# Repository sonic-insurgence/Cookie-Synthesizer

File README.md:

# Cookie Synthesizer

The Cookie is a small but powerful DIY synthesizer project.
It is derived from the Shruthi-1 DIY hybrid synthesizer by Émilie Gillet 
from Mutable Instruments. 
Slight modifications have been carried out concerning the PCB form factor, the track layout 
and the arrangement of components. 
The circuit is basically the same as the "Shruthi-Digital-v08" with a "Shruthi-Analog-SMR4-mkII-v02" 
filter board.

### User Manual
Learn how to operate your Cookie Synth by having a look at the 
[user manual of the original Shruthi-1](https://mutable-instruments.net/archive/shruthi/manual/).

### Patch Editor
There are several editors out there that can be used to tweak the sounds on your Cookie Synth. 
E. g. check out the one from 
[Ixox (Win / OS X)](https://github.com/Ixox/Shruthi-And-Ambika-Editors/releases).
You may also find a patch manager software useful to organize your many sounds. 
If you are on Windows you might give  
[ShruthiFi1_0 (Win)](https://sites.google.com/site/thesonicfunk/programs) a try, although 
I had some issues with it.

### Firmware
The Cookie provides full software compatibility with Shruthi-1. You can flash the 
microcontroller with the original firmware from MI or with an alternative firmware like 
YAM by bjoeri. The software provided in this repository is a slight modification of the latter.
* https://github.com/pichenettes/shruthi-1
* https://github.com/bjoeri/shruthi-1

### Authors
* Author of the derived work, i. e. the Cookie synthesizer, is Sonic Insurgence.
* Author of the original work, i. e. the Shruthi-1 synthesizer, is Émilie Gillet.
* Author of the alternative firmware YAM is bjoeri.

### License
The Cookie schematics and PCB design files are licensed under a CreativeCommons CC-BY-SA license.
See: http://creativecommons.org/licenses/by-sa/3.0/

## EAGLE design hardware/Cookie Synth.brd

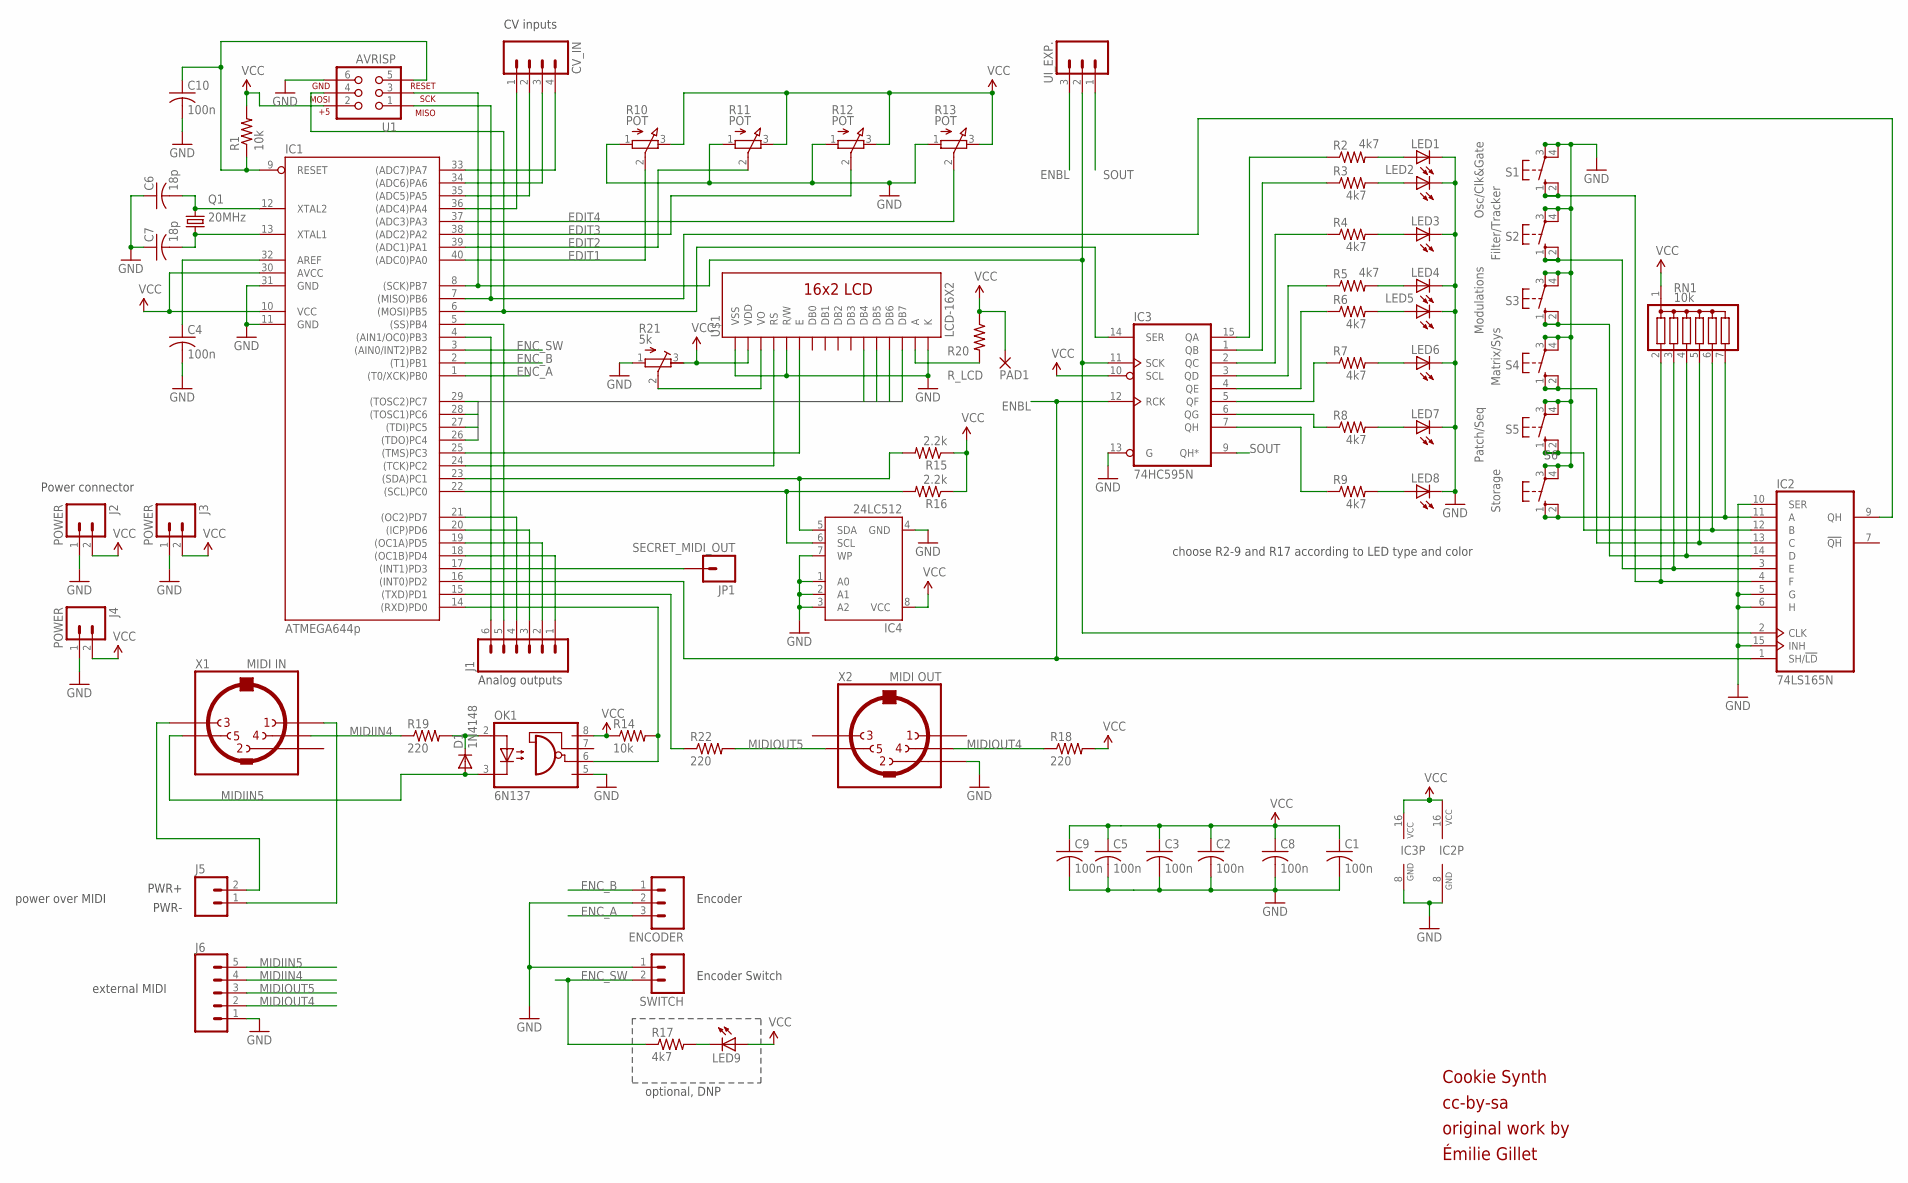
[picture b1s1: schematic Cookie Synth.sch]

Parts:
C1, C2, C3, C4, C5, C8, C9, C10: 100n; C025-024X044
C6, C7: 18p; C025-024X044
CV_IN: M04PTH; 1X04
D1: 1N4148; D-5
ENCODER: M03PTH; 1X03
IC1: ATMEGA644p; DIL40
IC2: 74LS165N; DIL16
IC3: 74HC595N; DIL16
IC4: 24LC512; DIL08
J1: M06SIP; 1X06
J2, J3, J4: POWER; 1X02
J5: M02PTH; 1X02
J6: CONN_05; 1X05
JP1: SECRET_MIDI_OUT; 1X01
LED1, LED2, LED3, LED4, LED5, LED6, LED7, LED8, LED9: LED3MM
OK1: 6N137; DIL08
PAD1: 1,6/0,8
Q1: 20MHz; HC49U-V
R1, R14: 10k; 0204/7
R2, R3, R4, R5, R6, R7, R8, R9, R17: 4k7; 0204/7
R10, R11, R12, R13: POT; POTI_ALPS_RK09
R15, R16: 2.2k; 0204/7
R18, R19, R22: 220; 0204/7
R20: R_LCD; 0204/7
R21: 5k; RTRIM3296X
RN1: 10k; SIL7
S1: Osc/Clk&Gate; B3F-40XX
S2: Filter/Tracker; B3F-40XX
S3: Modulations; B3F-40XX
S4: Matrix/Sys; B3F-40XX
S5: Patch/Seq; B3F-40XX
S6: Storage; B3F-40XX
SWITCH: M02PTH; 1X02
U1: AVRISP; 2X3
U$1: LCD-16X2
UI_EXP.: M03PTH; 1X03
X1: MIDI IN; MAB5SH
X2: MIDI OUT; MAB5SH

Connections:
EDIT1: IC1.40 ((ADC0)PA0), R10.2 (S)
EDIT2: IC1.39 ((ADC1)PA1), R11.2 (S)
EDIT3: IC1.38 ((ADC2)PA2), R12.2 (S)
EDIT4: IC1.37 ((ADC3)PA3), R13.2 (S)
ENBL: IC1.16 ((INT0)PD2), IC2.1 (SH/!LD), IC3.12 (RCK), UI_EXP..3
ENC_A: ENCODER.3, IC1.1 ((T0/XCK)PB0)
ENC_B: ENCODER.1, IC1.2 ((T1)PB1)
ENC_SW: IC1.3 ((AIN0/INT2)PB2), R17.1, SWITCH.2
GND: C1.2, C2.2, C3.2, C4.2, C5.2, C6.1, C7.1, C8.2, C9.2, C10.2, ENCODER.2, IC1.11 (GND), IC1.31 (GND), IC2.5 (G), IC2.6 (H), IC2.8 (GND), IC2.10 (SER), IC2.15 (INH), IC3.8 (GND), IC3.13 (G), IC4.1 (A0), IC4.2 (A1), IC4.3 (A2), IC4.4 (GND), IC4.7 (WP), J2.1, J3.1, J4.1, J6.1, LED1.K (C), LED2.K (C), LED3.K (C), LED4.K (C), LED5.K (C), LED6.K (C), LED7.K (C), LED8.K (C), OK1.5 (GND), R10.1 (A), R11.1 (A), R12.1 (A), R13.1 (A), R21.1 (E), S1.3, S1.4 (P1), S2.3, S2.4 (P1), S3.3, S3.4 (P1), S4.3, S4.4 (P1), S5.3, S5.4 (P1), S6.3, S6.4 (P1), SWITCH.1, U1.6, U$1.1 (VSS), U$1.5 (R/W), U$1.16 (K), X2.2
LCD_DATA1: IC1.26 ((TDO)PC4), U$1.11 (DB4)
LCD_DATA2: IC1.27 ((TDI)PC5), U$1.12 (DB5)
LCD_DATA3: IC1.28 ((TOSC1)PC6), U$1.13 (DB6)
LCD_DATA4: IC1.29 ((TOSC2)PC7), U$1.14 (DB7)
MIDIIN4: J6.4, R19.1, X1.4
MIDIIN5: D1.A, J6.5, OK1.3 (C), X1.5
MIDIOUT4: J6.2, R18.1, X2.4
MIDIOUT5: J6.3, R22.2, X2.5
unnamed: IC3.2 (QC), R4.1
unnamed: IC1.24 ((TCK)PC2), U$1.4 (RS)
unnamed: IC2.11 (A), RN1.7, S6.1 (S), S6.2 (S1)
unnamed: LED9.K (C), R17.2
unnamed: IC2.3 (E), RN1.3, S2.1 (S), S2.2 (S1)
unnamed: C10.1, IC1.9 (RESET), R1.1, U1.5
unnamed: C4.1, IC1.32 (AREF)
unnamed: IC1.8 ((SCK)PB7), IC2.2 (CLK), IC3.11 (SCK), U1.3, UI_EXP..2
unnamed: IC1.7 ((MISO)PB6), IC2.9 (QH), U1.1
unnamed: CV_IN.1, IC1.36 ((ADC4)PA4)
unnamed: CV_IN.2, IC1.35 ((ADC5)PA5)
unnamed: CV_IN.3, IC1.34 ((ADC6)PA6)
unnamed: CV_IN.4, IC1.33 ((ADC7)PA7)
unnamed: R20.2, U$1.15 (A)
unnamed: IC1.4 ((AIN1/OC0)PB3), J1.6
unnamed: IC1.5 ((SS)PB4), J1.5
unnamed: IC1.18 ((OC1B)PD4), J1.1
unnamed: IC1.19 ((OC1A)PD5), J1.2
unnamed: IC1.20 ((ICP)PD6), J1.3
unnamed: IC1.21 ((OC2)PD7), J1.4
unnamed: J5.1, X1.1
unnamed: IC1.17 ((INT1)PD3), JP1.1
unnamed: IC1.23 ((SDA)PC1), IC4.5 (SDA), R15.2
unnamed: D1.C, OK1.2 (A), R19.2
unnamed: J5.2, X1.3
unnamed: IC3.15 (QA), R2.1
unnamed: IC3.1 (QB), R3.1
unnamed: IC1.22 ((SCL)PC0), IC4.6 (SCL), R16.2
unnamed: IC3.3 (QD), R5.1
unnamed: IC3.4 (QE), R6.1
unnamed: IC3.5 (QF), R7.1
unnamed: IC3.7 (QH), R9.1
unnamed: IC3.6 (QG), R8.1
unnamed: LED1.A, R2.2
unnamed: LED2.A, R3.2
unnamed: LED3.A, R4.2
unnamed: LED4.A, R5.2
unnamed: LED5.A, R6.2
unnamed: LED6.A, R7.2
unnamed: LED7.A, R8.2
unnamed: LED8.A, R9.2
unnamed: IC1.6 ((MOSI)PB5), IC3.14 (SER), U1.4
unnamed: IC2.4 (F), RN1.2, S1.1 (S), S1.2 (S1)
unnamed: IC2.14 (D), RN1.4, S3.1 (S), S3.2 (S1)
unnamed: IC2.13 (C), RN1.5, S4.1 (S), S4.2 (S1)
unnamed: IC2.12 (B), RN1.6, S5.1 (S), S5.2 (S1)
unnamed: IC1.25 ((TMS)PC3), U$1.6 (E)
unnamed: R21.2 (S), U$1.3 (VO)
unnamed: C7.2, IC1.13 (XTAL1), Q1.1
unnamed: C6.2, IC1.12 (XTAL2), Q1.2
RXD: IC1.14 ((RXD)PD0), OK1.6 (VO), R14.2
SOUT: IC3.9 (QH*), UI_EXP..1
TXD: IC1.15 ((TXD)PD1), R22.1
VCC: C1.1, C2.1, C3.1, C5.1, C8.1, C9.1, IC1.10 (VCC), IC1.30 (AVCC), IC2.16 (VCC), IC3.10 (SCL), IC3.16 (VCC), IC4.8 (VCC), J2.2, J3.2, J4.2, LED9.A, OK1.8 (VCC), PAD1.1, R1.2, R10.3 (E), R11.3 (E), R12.3 (E), R13.3 (E), R14.1, R15.1, R16.1, R18.2, R20.1, R21.3 (A), RN1.1, U1.2, U$1.2 (VDD)

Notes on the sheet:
CV inputs
Power connector
Analog outputs
cc-by-sa
original work by
PWR-
PWR+
Encoder
Encoder Switch
Émilie Gillet
Cookie Synth
external MIDI
power over MIDI
optional, DNP
choose R2-9 and R17 according to LED type and color

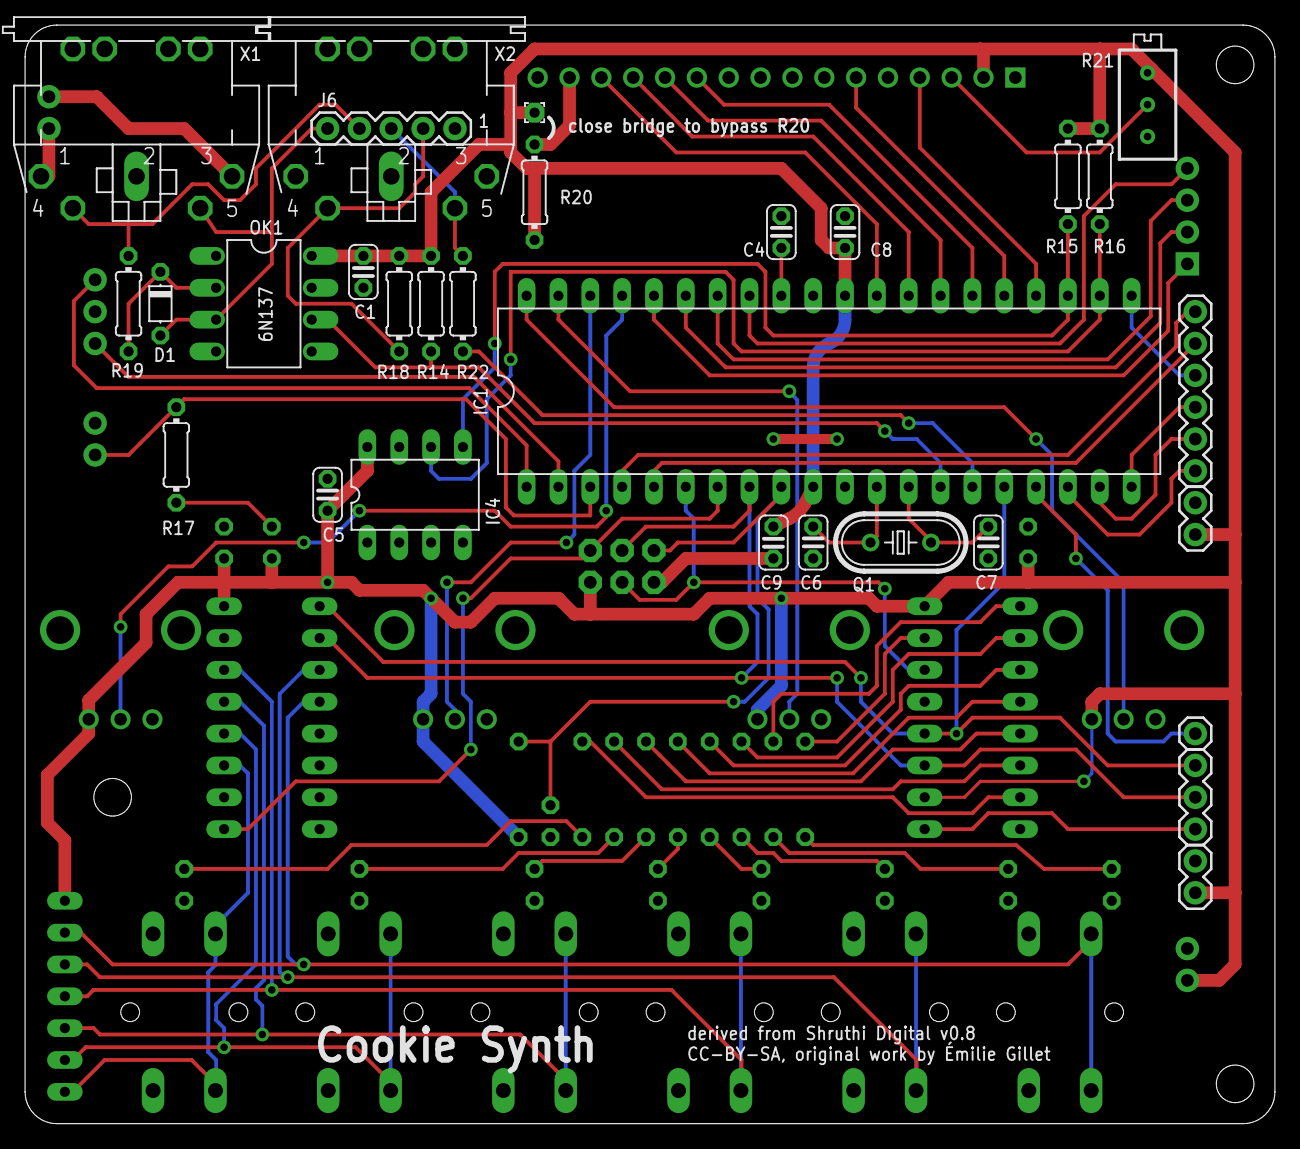
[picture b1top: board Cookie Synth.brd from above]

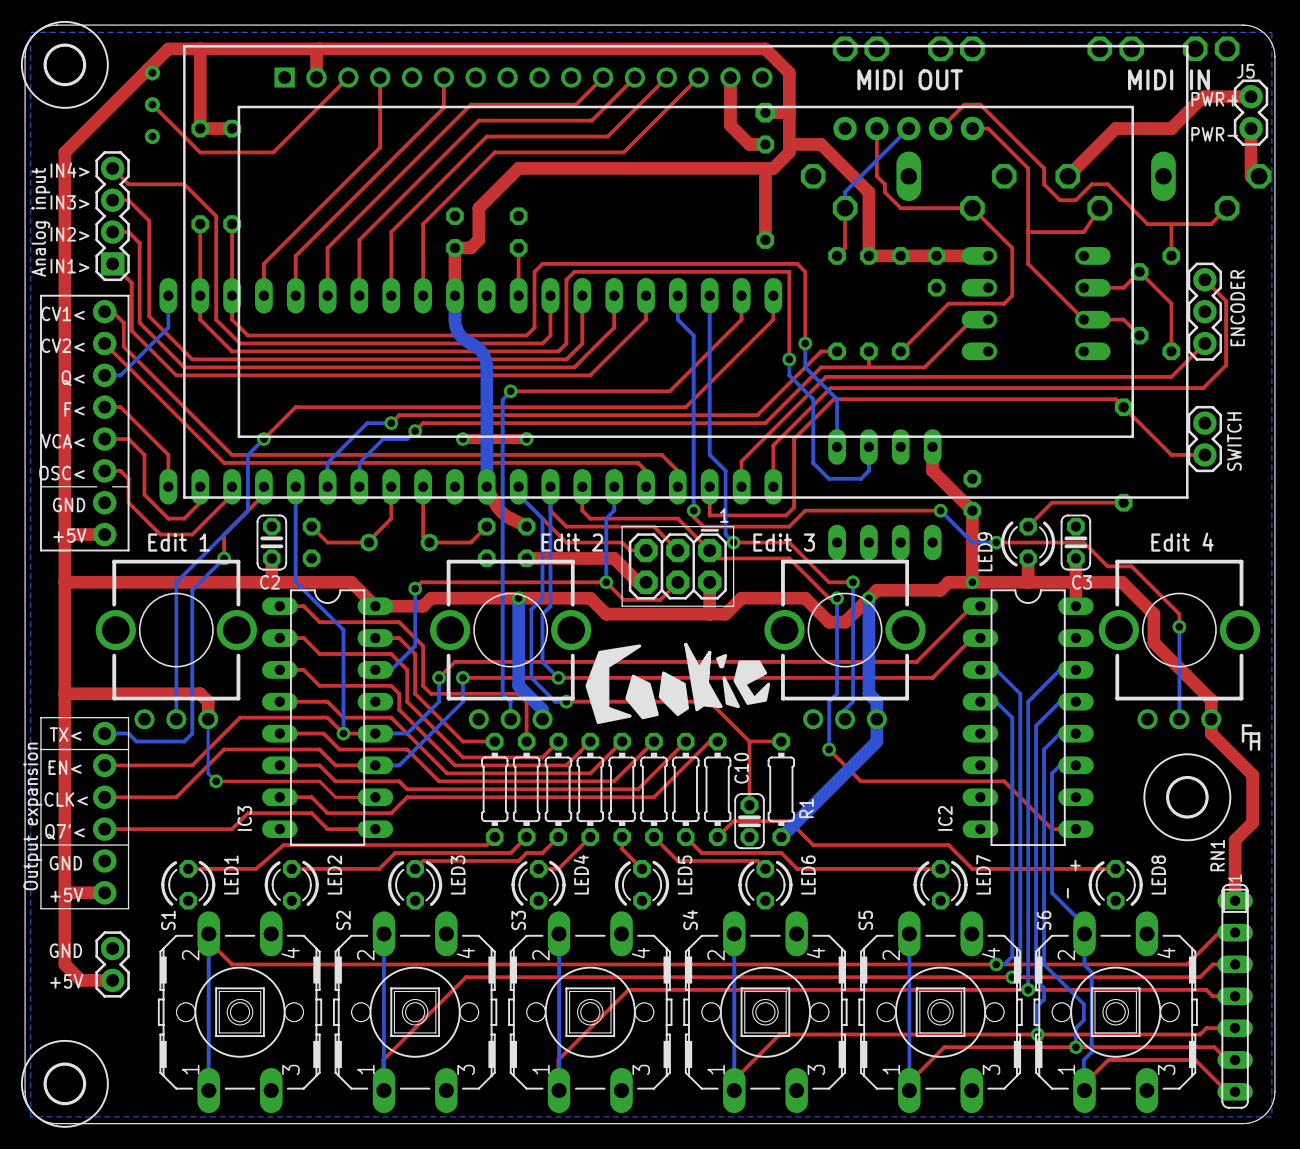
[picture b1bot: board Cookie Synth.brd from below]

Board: 2 copper layers, 99.7 x 87.6 mm, 74 parts (44 on the bottom side), 71 nets.

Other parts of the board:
U$2, U$3, U$4: 3,0

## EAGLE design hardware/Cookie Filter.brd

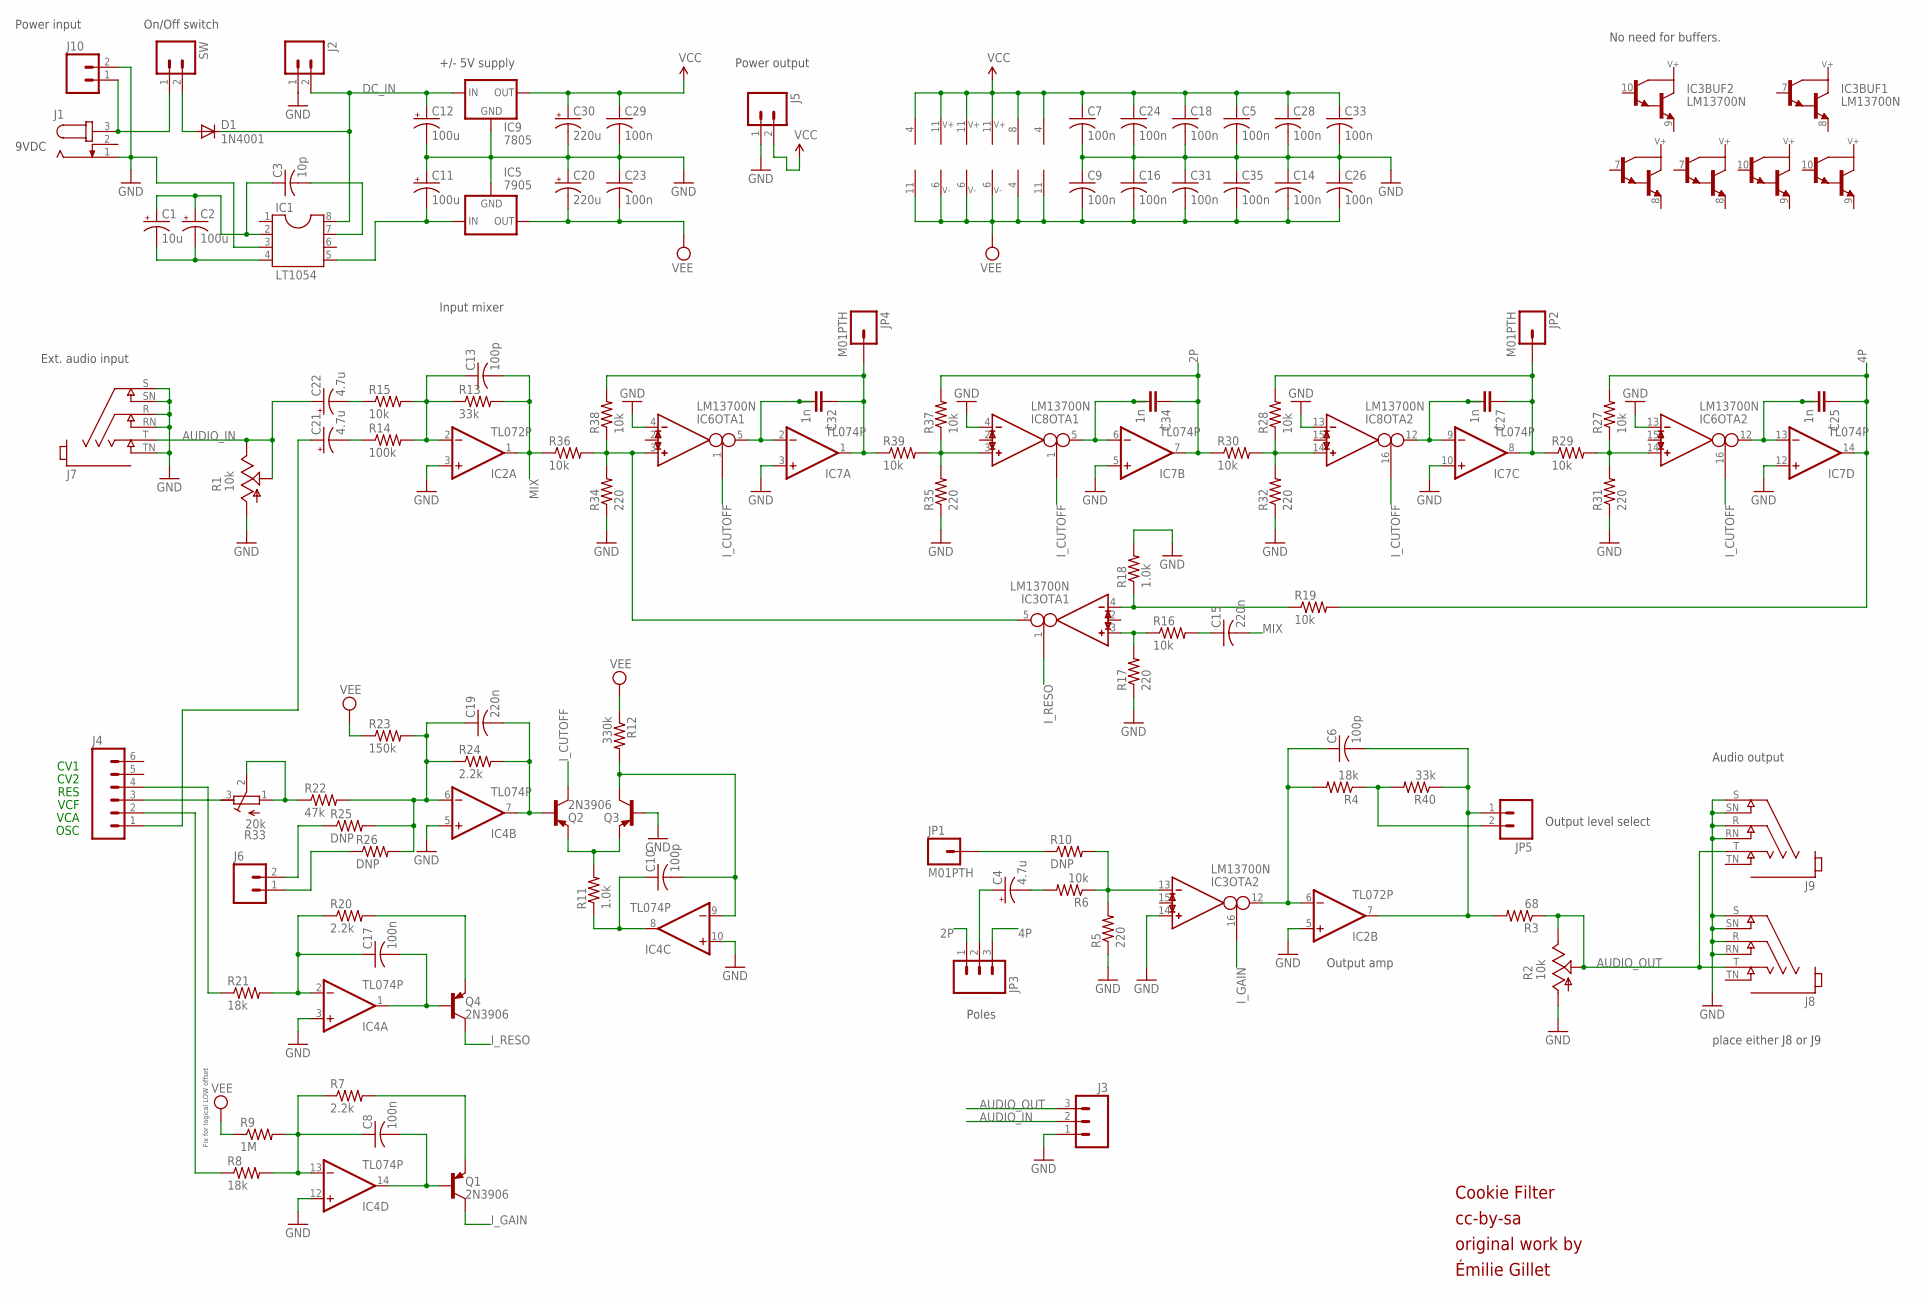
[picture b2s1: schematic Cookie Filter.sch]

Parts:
C1: 10u; E2,5-5
C2, C11, C12: 100u; E2,5-6
C3: 10p; C025-025X050
C4, C21, C22: 4.7u; E2,5-6
C5, C7, C8, C9, C14, C16, C17, C18, C23, C24, C26, C28, C29, C31, C33, C35: 100n; C025-025X050
C6, C10, C13: 100p; C025-025X050
C15, C19: 220n; C025-025X050
C20, C30: 220u; E2,5-7
C25, C27, C32, C34: 1n; C2.5/5-2
D1: 1N4001; DO41-10
IC1: LT1054; DIL08
IC2: TL072P; DIL08
IC3, IC6, IC8: LM13700N; DIL16
IC4, IC7: TL074P; DIL14
IC5: 7905; 79XXS
IC9: 7805; 78XXS
J1: JACK-PLUG1; SPC4078
J2, J5, J6, J10: M02PTH; 1X02
J3: M03PTH; 1X03
J4: M06SIP; 1X06
J7, J8, J9: NRJ4HF; NRJ6HF
JP1, JP2, JP4: M01PTH; 1X01
JP3: M03PTH; 1X03
JP5: M02PTH; 1X02
Q1, Q2, Q3, Q4: 2N3906; TO92-
R1, R2: 10k; CABLE_POT_6MM
R3: 68; 0204/7
R4, R8, R21: 18k; 0204/7
R5, R17, R31, R32, R34, R35: 220; 0204/7
R6, R15, R16, R19, R27, R28, R29, R30, R36, R37, R38, R39: 10k; 0204/7
R7, R20, R24: 2.2k; 0204/7
R9: 1M; 0204/7
R10, R25, R26: DNP; 0204V
R11, R18: 1.0k; 0204/7
R12: 330k; 0204/7
R13, R40: 33k; 0204/7
R14: 100k; 0204/7
R22: 47k; 0204/7
R23: 150k; 0204/7
R33: 20k; RTRIM3296X
SW: M02PTH; 1X02

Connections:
2P: C34.1, IC7.7 (OUT), JP3.1, R30.1, R37.2
4P: C25.1, IC7.14 (OUT), JP3.3, R19.2, R27.2
AUDIO_IN: C22.+, J3.2, J7.T, R1.E, R1.S
AUDIO_OUT: J3.3, J8.T, J9.T, R2.E, R2.S, R3.1
DC_IN: C12.+, D1.C, IC1.8, IC9.IN, J2.2
DC_NEG: C11.-, IC1.5, IC5.IN
GND: C5.2, C7.2, C9.1, C11.+, C12.-, C14.1, C16.1, C18.2, C20.+, C23.1, C24.2, C26.1, C28.2, C29.2, C30.-, C31.1, C33.2, C35.1, IC1.3, IC2.3 (+IN), IC2.5 (+IN), IC3.14 (IN_P), IC4.3 (+IN), IC4.5 (+IN), IC4.10 (+IN), IC4.12 (+IN), IC5.GND, IC6.4 (IN_N), IC6.13 (IN_N), IC7.3 (+IN), IC7.5 (+IN), IC7.10 (+IN), IC7.12 (+IN), IC8.4 (IN_N), IC8.13 (IN_N), IC9.GND, J1.1, J2.1, J3.1, J5.1, J7.R, J7.RN, J7.S, J7.SN, J7.TN, J8.R, J8.RN, J8.S, J8.SN, J9.R, J9.RN, J9.S, J9.SN, J10.2, Q3.2 (B), R1.A, R2.A, R5.1, R17.1, R18.2, R31.1, R32.1, R34.1, R35.1
I_CUTOFF: IC6.1 (I_BIAS), IC6.16 (I_BIAS), IC8.1 (I_BIAS), IC8.16 (I_BIAS), Q2.1 (C)
I_GAIN: IC3.16 (I_BIAS), Q1.1 (C)
I_RESO: IC3.1 (I_BIAS), Q4.1 (C)
MIX: C13.2, C15.2, IC2.1 (OUT), R13.2, R36.1
unnamed: JP1.1, R10.1
unnamed: C19.2, IC4.7 (OUT), Q2.2 (B), R24.2
unnamed: R22.1, R33.1 (E), R33.2 (S)
unnamed: J4.3, R33.3 (A)
unnamed: JP5.2, R4.1, R40.2
unnamed: C13.1, IC2.2 (-IN), R13.1, R14.2, R15.2
unnamed: Q2.3 (E), Q3.3 (E), R11.2
unnamed: C4.+, JP3.2
unnamed: C10.1, IC4.8 (OUT), R11.1
unnamed: C10.2, IC4.9 (-IN), Q3.1 (C), R12.2
unnamed: J4.4, R21.1
unnamed: IC3.5 (OUT), IC6.3 (IN_P), R34.2, R36.2, R38.1
unnamed: J1.3, J10.1, SW.1
unnamed: C32.1, IC7.1 (OUT), JP4.1, R38.2, R39.1
unnamed: IC8.3 (IN_P), R35.2, R37.1, R39.2
unnamed: C4.-, R6.2
unnamed: J6.2, R25.1
unnamed: IC8.14 (IN_P), R28.1, R30.2, R32.2
unnamed: C15.1, R16.2
unnamed: J6.1, R26.1
unnamed: IC6.14 (IN_P), R27.1, R29.2, R31.2
unnamed: C27.1, IC7.8 (OUT), JP2.1, R28.2, R29.1
unnamed: C32.2, C32.3, IC6.5 (OUT), IC7.2 (-IN)
unnamed: C34.2, C34.3, IC7.6 (-IN), IC8.5 (OUT)
unnamed: IC3.4 (IN_N), R18.1, R19.1
unnamed: C17.2, IC4.1 (OUT), Q4.2 (B)
unnamed: C8.2, IC4.14 (OUT), Q1.2 (B)
unnamed: IC3.3 (IN_P), R16.1, R17.2
unnamed: IC3.13 (IN_N), R5.2, R6.1, R10.2
unnamed: C21.+, J4.1
unnamed: C27.2, C27.3, IC7.9 (-IN), IC8.12 (OUT)
unnamed: C25.2, C25.3, IC6.12 (OUT), IC7.13 (-IN)
unnamed: C21.-, R14.1
unnamed: C19.1, IC4.6 (-IN), R22.2, R23.2, R24.1, R25.2, R26.2
unnamed: J4.2, R8.1
unnamed: C1.+, C2.+, C3.1, IC1.2
unnamed: C1.-, C2.-, IC1.4
unnamed: C3.2, IC1.7
unnamed: C8.1, IC4.13 (-IN), R7.1, R8.2, R9.2
unnamed: C17.1, IC4.2 (-IN), R20.1, R21.2
unnamed: D1.A, SW.2
unnamed: Q4.3 (E), R20.2
unnamed: C6.2, IC2.7 (OUT), JP5.1, R3.2, R40.1
unnamed: Q1.3 (E), R7.2
unnamed: C6.1, IC2.6 (-IN), IC3.12 (OUT), R4.2
unnamed: C22.-, R15.1
VCC: C5.1, C7.1, C18.1, C24.1, C28.1, C29.1, C30.+, C33.1, IC2.8 (V+), IC3.11 (V+), IC4.4 (V+), IC6.11 (V+), IC7.4 (V+), IC8.11 (V+), IC9.OUT, J5.2
VEE: C9.2, C14.2, C16.2, C20.-, C23.2, C26.2, C31.2, C35.2, IC2.4 (V-), IC3.6 (V-), IC4.11 (V-), IC5.OUT, IC6.6 (V-), IC7.11 (V-), IC8.6 (V-), R9.1, R12.1, R23.1

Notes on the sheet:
Power output
OSC
VCA
VCF
RES
original work by
Output amp
CV1
CV2
Input mixer
+/- 5V supply
No need for buffers.
Fix for logical LOW offset
Émilie Gillet
Ext. audio input
cc-by-sa
Cookie Filter
Audio output
Power input
Poles
Output level select
9VDC
On/Off switch
place either J8 or J9

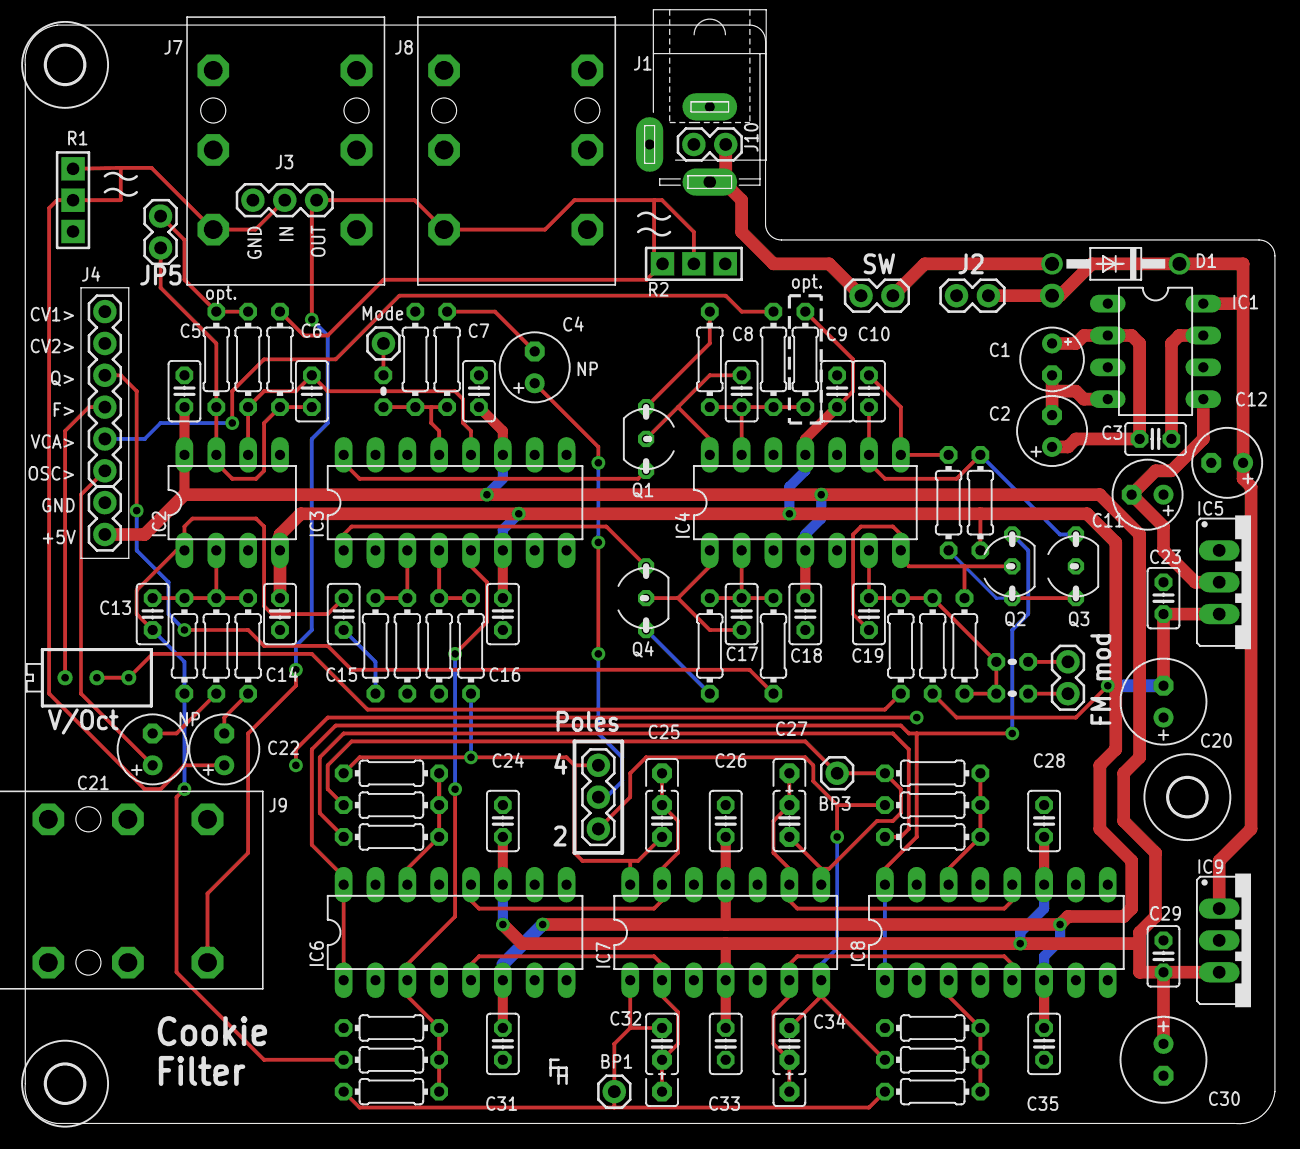
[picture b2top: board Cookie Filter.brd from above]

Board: 2 copper layers, 99.7 x 87.6 mm, 108 parts (0 on the bottom side), 59 nets.

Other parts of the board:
U$1, U$4, U$5: 3,0

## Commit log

2020-09-09 name of filter board corrected
2020-10-04 Cookie firmware added
2020-10-04 note on C4 added
2020-10-12 pictures added
2022-12-07 .gitignore added
    ignore .DS_Store files

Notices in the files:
hardware/Cookie Filter.brd:
CC-BY-SA, original work by Émilie Gillet
parts and their libraries:
Connectors: Licensing: Creative Commons ShareAlike 4.0 International - https://creativecommons.org/licenses/by-sa/4.0
